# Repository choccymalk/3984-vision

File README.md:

Derived from jkiv/cm4-carriers\

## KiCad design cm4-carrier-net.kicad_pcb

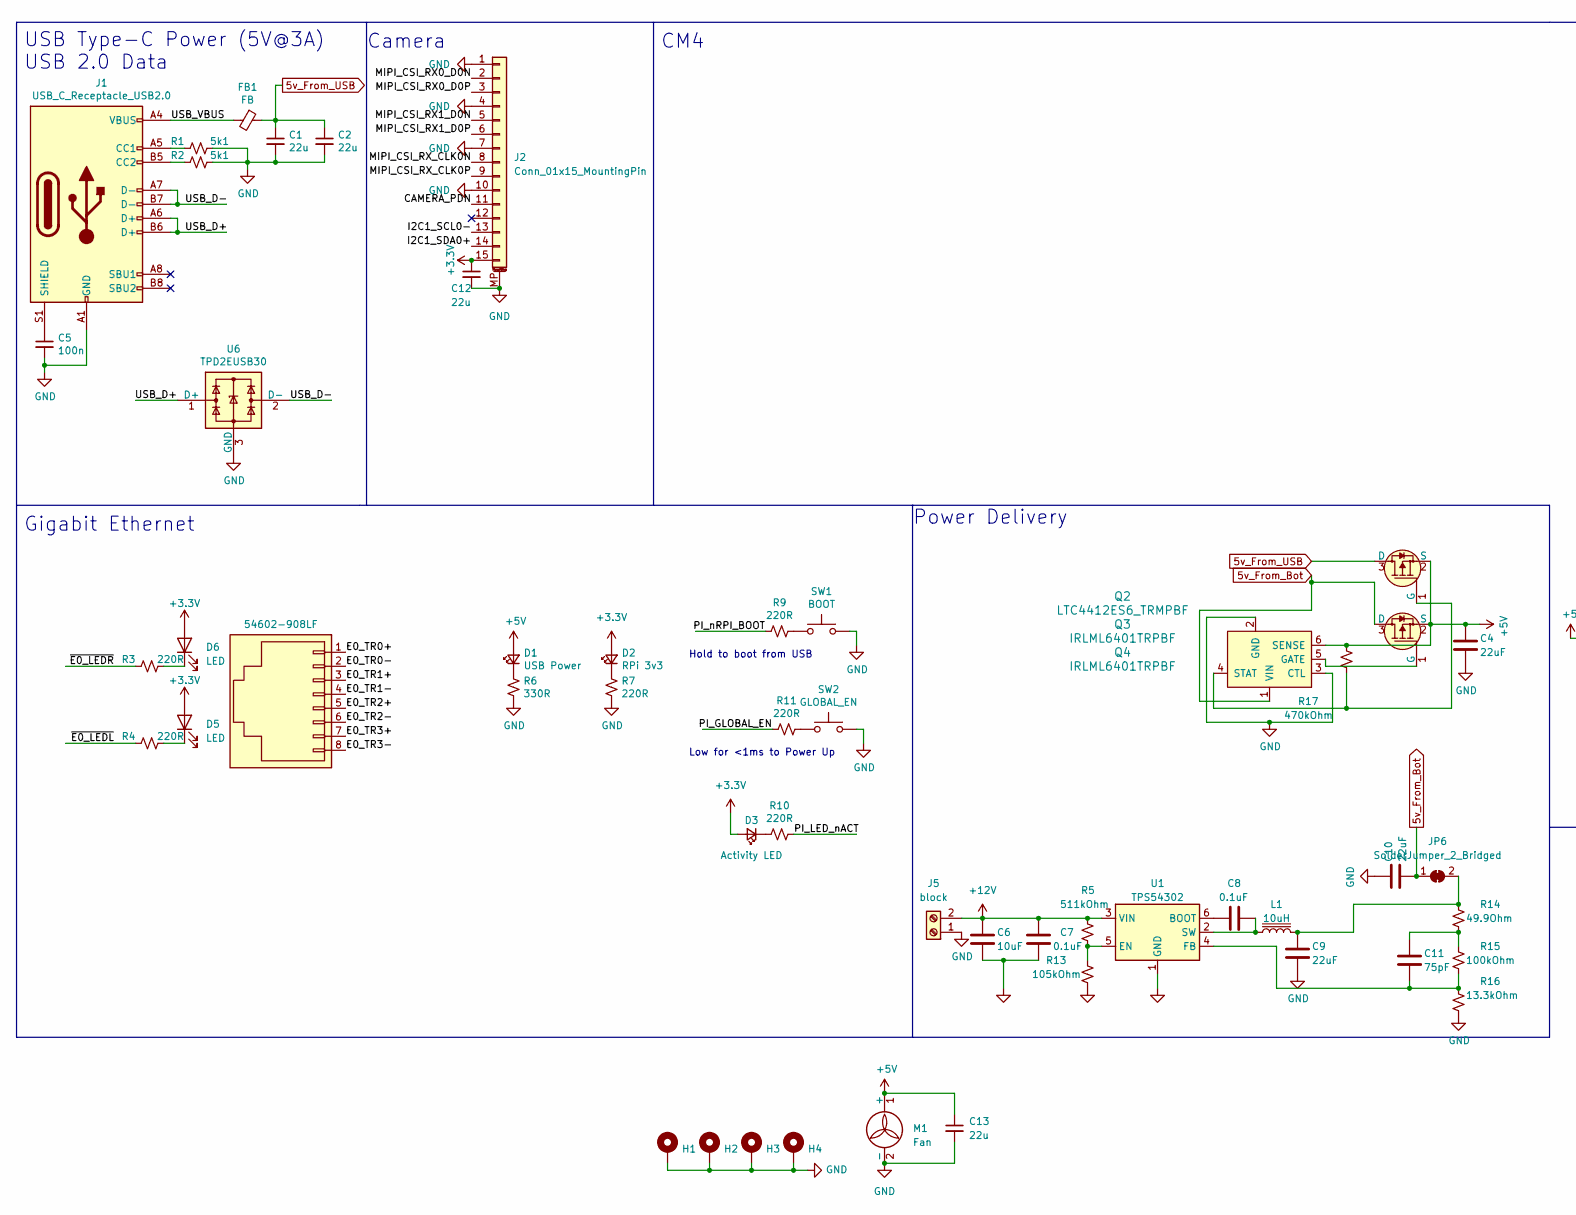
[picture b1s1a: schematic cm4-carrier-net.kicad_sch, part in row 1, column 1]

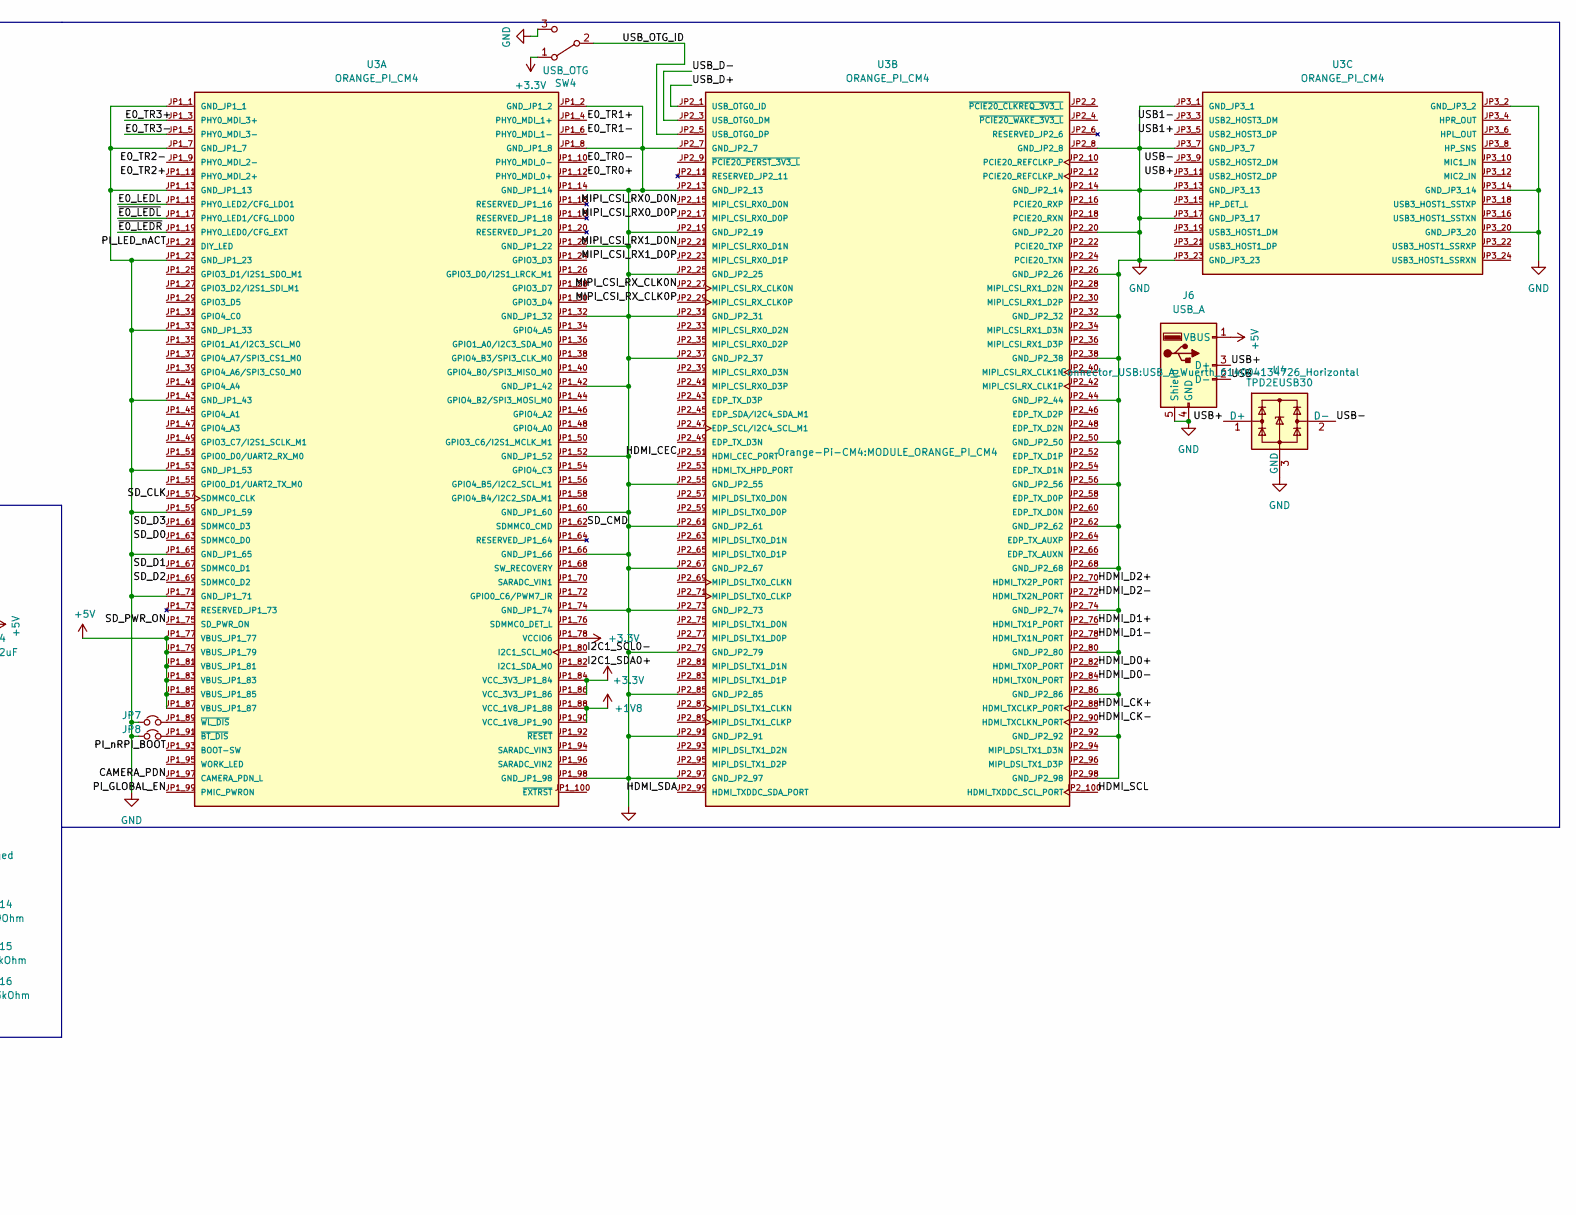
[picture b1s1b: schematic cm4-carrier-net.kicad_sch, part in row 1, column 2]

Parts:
C1, C2, C12, C13: 22u; C_0805_2012Metric
C4, C9, C10: 22uF; C_1206_3216Metric
C5: 100n; C_0805_2012Metric
C6: 10uF; C_1206_3216Metric
C7, C8: 0.1uF; C_1206_3216Metric
C11: 75pF; C_1206_3216Metric
D1: USB Power; LED_0603_1608Metric
D2: RPi 3v3; LED_0603_1608Metric
D3: Activity LED; LED_0603_1608Metric
D5, D6: LED; D_1206_3216Metric_Pad1.42x1.75mm_HandSolder
FB1: FB; L_0805_2012Metric
H1, H2, H3, H4: MountingHole_Pad; MountingHole_2.7mm_M2.5_Pad_Via
J1: USB_C_Receptacle_USB2.0; USB_C_Receptacle_G-Switch_GT-USB-7010ASV
J2: Conn_01x15_MountingPin; Molex_200528-0150_1x15-1MP_P1.00mm_Horizontal
J3: 54602-908LF; Ethernet_Jack_54602-908LF; MPN 54602-908LF; Digi-Key_PN 609-1046-ND
J5: block; TerminalBlock_4Ucon_1x02_P3.50mm_Vertical
J6: USB_A; USB_A_Wuerth_614004134726_Horizontal
JP6: SolderJumper_2_Bridged; SolderJumper-2_P1.3mm_Bridged2Bar_RoundedPad1.0x1.5mm
JP7: ~WL_nDisable; SolderJumper-2_P1.3mm_Bridged2Bar_Pad1.0x1.5mm
JP8: ~BT_nDisable; SolderJumper-2_P1.3mm_Bridged2Bar_Pad1.0x1.5mm
L1: 10uH; L_6.3x6.3_H3
M1: Fan; PinHeader_1x02_P2.54mm_Vertical
Q2: LTC4412ES6_TRMPBF; SOT-23-6; MPN LTC4412ES6#TRMPBF; Digi-Key_PN LTC4412ES6#TRMPBFCT-ND
Q3, Q4: IRLML6401TRPBF; SOT-23-3; MPN IRLML6401TRPBF; Digi-Key_PN IRLML6401PBFCT-ND
R1, R2: 5k1; R_0603_1608Metric
R3, R4, R7, R9, R10, R11: 220R; R_0603_1608Metric
R5: 511kOhm; R_0603_1608Metric
R6: 330R; R_0603_1608Metric
R13: 105kOhm; R_0603_1608Metric
R14: 49.9Ohm; R_0603_1608Metric
R15: 100kOhm; R_0603_1608Metric
R16: 13.3kOhm; R_0603_1608Metric
R17: 470kOhm; R_0603_1608Metric
SW1: BOOT; SW_SPST_B3U-1000P
SW2: GLOBAL_EN; SW_SPST_B3U-1000P
SW4: USB_OTG; SW_SPDT_CK-JS102011SAQN
U1: TPS54302; SOT-23-6
U3: ORANGE_PI_CM4; MODULE_ORANGE_PI_CM4; PARTREV v1.2
U4, U6: TPD2EUSB30; Texas_DRT-3

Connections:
5v_From_Bot: C10.2, JP6.1 (A), Q2.1 (VIN), Q3.3 (D)
5v_From_USB: C1.1, C2.1, FB1.1, Q4.3 (D)
+1V8: U3.JP1_88 (VCC_1V8_JP1_88), U3.JP1_90 (VCC_1V8_JP1_90)
+3.3V: C12.1, D2.2 (A), D3.2 (A), D5.2 (A), D6.2 (A), SW4.1 (A), U3.JP1_78 (VCCIO6), U3.JP1_84 (VCC_3V3_JP1_84), U3.JP1_86 (VCC_3V3_JP1_86); also elsewhere on the board
+5V: C4.1, C13.1, D1.2 (A), J6.1 (VBUS), M1.1 (+), Q2.6 (SENSE), Q3.2 (S), Q4.2 (S), R17.1, U3.JP1_77 (VBUS_JP1_77), U3.JP1_79 (VBUS_JP1_79), U3.JP1_81 (VBUS_JP1_81), U3.JP1_83 (VBUS_JP1_83), U3.JP1_85 (VBUS_JP1_85), U3.JP1_87 (VBUS_JP1_87)
+12V: C6.1, C7.1, J5.2, R5.1, U1.3 (VIN)
/CAMERA_PDN: U3.JP1_97 (CAMERA_PDN_L); also elsewhere on the board
/E0_LEDL: U3.JP1_15 (PHY0_LED2/CFG_LDO1)
/E0_TR0+: J3.1, U3.JP1_12 (PHY0_MDI_0+)
/E0_TR0-: J3.2, U3.JP1_10 (PHY0_MDI_0-)
/E0_TR1+: J3.3, U3.JP1_4 (PHY0_MDI_1+)
/E0_TR1-: J3.4, U3.JP1_6 (PHY0_MDI_1-)
/E0_TR2+: J3.5, U3.JP1_11 (PHY0_MDI_2+)
/E0_TR2-: J3.6, U3.JP1_9 (PHY0_MDI_2-)
/E0_TR3+: J3.7, U3.JP1_3 (PHY0_MDI_3+)
/E0_TR3-: J3.8, U3.JP1_5 (PHY0_MDI_3-)
/HDMI_CEC: U3.JP2_51 (HDMI_CEC_PORT)
/HDMI_CK+: U3.JP2_88 (HDMI_TXCLKP_PORT)
/HDMI_CK-: U3.JP2_90 (HDMI_TXCLKN_PORT)
/HDMI_D0+: U3.JP2_82 (HDMI_TX0P_PORT)
/HDMI_D0-: U3.JP2_84 (HDMI_TX0N_PORT)
/HDMI_D1+: U3.JP2_76 (HDMI_TX1P_PORT)
/HDMI_D1-: U3.JP2_78 (HDMI_TX1N_PORT)
/HDMI_D2+: U3.JP2_70 (HDMI_TX2P_PORT)
/HDMI_D2-: U3.JP2_72 (HDMI_TX2N_PORT)
/HDMI_SCL: U3.JP2_100 (HDMI_TXDDC_SCL_PORT)
/HDMI_SDA: U3.JP2_99 (HDMI_TXDDC_SDA_PORT)
/I2C1_SCL0-: U3.JP1_80 (I2C1_SCL_M0); also elsewhere on the board
/I2C1_SDA0+: U3.JP1_82 (I2C1_SDA_M0); also elsewhere on the board
/MIPI_CSI_RX0_D0N: U3.JP2_15 (MIPI_CSI_RX0_D0N); also elsewhere on the board
/MIPI_CSI_RX0_D0P: U3.JP2_17 (MIPI_CSI_RX0_D0P); also elsewhere on the board
/MIPI_CSI_RX1_D0N: U3.JP2_21 (MIPI_CSI_RX0_D1N); also elsewhere on the board
/MIPI_CSI_RX1_D0P: U3.JP2_23 (MIPI_CSI_RX0_D1P); also elsewhere on the board
/MIPI_CSI_RX_CLK0N: U3.JP2_27 (MIPI_CSI_RX_CLK0N); also elsewhere on the board
/MIPI_CSI_RX_CLK0P: U3.JP2_29 (MIPI_CSI_RX_CLK0P); also elsewhere on the board
/PI_GLOBAL_EN: R11.2, U3.JP1_99 (PMIC_PWRON)
/PI_LED_nACT: R10.1, U3.JP1_21 (DIY_LED)
/PI_nRPI_BOOT: R9.2, U3.JP1_93 (BOOT-SW)
/SD_CLK: U3.JP1_57 (SDMMC0_CLK)
/SD_CMD: U3.JP1_62 (SDMMC0_CMD)
/SD_D0: U3.JP1_63 (SDMMC0_D0)
/SD_D1: U3.JP1_67 (SDMMC0_D1)
/SD_D2: U3.JP1_69 (SDMMC0_D2)
/SD_D3: U3.JP1_61 (SDMMC0_D3)
/SD_PWR_ON: U3.JP1_75 (SD_PWR_ON)
/USB1+: U3.JP3_5 (USB2_HOST3_DP)
/USB1-: U3.JP3_3 (USB2_HOST3_DM)
/USB+: J6.3 (D+), U3.JP3_11 (USB2_HOST2_DP), U4.1 (D+)
/USB-: J6.2 (D-), U3.JP3_9 (USB2_HOST2_DM), U4.2 (D-)
/USB_D+: J1.A6 (D+), J1.B6 (D+), U3.JP2_1 (USB_OTG0_ID), U6.1 (D+)
/USB_D-: J1.A7 (D-), J1.B7 (D-), U3.JP2_3 (USB_OTG0_DM), U6.2 (D-)
/USB_OTG_ID: SW4.2 (B), U3.JP2_5 (USB_OTG0_DP)
/USB_VBUS: FB1.2, J1.A4 (VBUS), J1.A9 (VBUS), J1.B4 (VBUS), J1.B9 (VBUS)
/~E0_LEDL: R4.2, U3.JP1_17 (PHY0_LED1/CFG_LDO0)
/~E0_LEDR: R3.2, U3.JP1_19 (PHY0_LED0/CFG_EXT)
GND: C1.2, C2.2, C4.2, C5.2, C6.2, C7.2, C9.2, C10.1, C12.2, C13.2, H1.1, H2.1, H3.1, H4.1, J1.A1 (GND), J1.A12 (GND), J1.B1 (GND), J1.B12 (GND), J5.1, J6.4 (GND), J6.5 (Shield), JP7.1, JP8.1, M1.2 (-), Q2.2 (GND), Q2.3 (CTL), R1.1, R2.1, R6.2, R7.2, R13.2, R16.2, SW1.2, SW2.2, SW4.3 (C), U1.1 (GND), U3.JP1_1 (GND_JP1_1), U3.JP1_2 (GND_JP1_2), U3.JP1_7 (GND_JP1_7), U3.JP1_8 (GND_JP1_8), U3.JP1_13 (GND_JP1_13), U3.JP1_14 (GND_JP1_14), U3.JP1_22 (GND_JP1_22), U3.JP1_23 (GND_JP1_23), U3.JP1_32 (GND_JP1_32), U3.JP1_33 (GND_JP1_33), U3.JP1_42 (GND_JP1_42), U3.JP1_43 (GND_JP1_43), U3.JP1_52 (GND_JP1_52), U3.JP1_53 (GND_JP1_53), U3.JP1_59 (GND_JP1_59), U3.JP1_60 (GND_JP1_60), U3.JP1_65 (GND_JP1_65), U3.JP1_66 (GND_JP1_66), U3.JP1_71 (GND_JP1_71), U3.JP1_74 (GND_JP1_74), U3.JP1_98 (GND_JP1_98), U3.JP2_7 (GND_JP2_7), U3.JP2_8 (GND_JP2_8), U3.JP2_13 (GND_JP2_13), U3.JP2_14 (GND_JP2_14), U3.JP2_19 (GND_JP2_19), U3.JP2_20 (GND_JP2_20), U3.JP2_25 (GND_JP2_25), U3.JP2_26 (GND_JP2_26), U3.JP2_31 (GND_JP2_31), U3.JP2_32 (GND_JP2_32), U3.JP2_37 (GND_JP2_37), U3.JP2_38 (GND_JP2_38), U3.JP2_44 (GND_JP2_44), U3.JP2_50 (GND_JP2_50), U3.JP2_55 (GND_JP2_55), U3.JP2_56 (GND_JP2_56), U3.JP2_61 (GND_JP2_61), U3.JP2_62 (GND_JP2_62), U3.JP2_67 (GND_JP2_67), U3.JP2_68 (GND_JP2_68), U3.JP2_73 (GND_JP2_73), U3.JP2_74 (GND_JP2_74), U3.JP2_79 (GND_JP2_79), U3.JP2_80 (GND_JP2_80), U3.JP2_85 (GND_JP2_85), U3.JP2_86 (GND_JP2_86), U3.JP2_91 (GND_JP2_91), U3.JP2_92 (GND_JP2_92), U3.JP2_97 (GND_JP2_97), U3.JP2_98 (GND_JP2_98), U3.JP3_1 (GND_JP3_1), U3.JP3_2 (GND_JP3_2), U3.JP3_7 (GND_JP3_7), U3.JP3_13 (GND_JP3_13), U3.JP3_14 (GND_JP3_14), U3.JP3_17 (GND_JP3_17), U3.JP3_20 (GND_JP3_20), U3.JP3_23 (GND_JP3_23), U4.3 (GND), U6.3 (GND); also elsewhere on the board
unnamed: C11.1, R14.2, R15.1
unnamed: D1.1 (K), R6.1
unnamed: D2.1 (K), R7.1
unnamed: D3.1 (K), R10.2
unnamed: D5.1 (K), R4.1
unnamed: D6.1 (K), R3.1
unnamed: J1.A5 (CC1), R1.2
unnamed: J1.B5 (CC2), R2.2
unnamed: C5.1, J1.S1 (SHIELD)
unnamed: C9.1, JP6.2 (B), L1.2, R14.1
unnamed: Q2.5 (GATE), Q3.1 (G)
unnamed: Q2.4 (STAT), Q4.1 (G), R17.2
unnamed: R9.1, SW1.1
unnamed: R11.1, SW2.1
unnamed: C8.1, U1.6 (BOOT)
unnamed: R5.2, R13.1, U1.5 (EN)
unnamed: C11.2, R15.2, R16.1, U1.4 (FB)
unnamed: C8.2, L1.1, U1.2 (SW)
unnamed: JP8.2, U3.JP1_91 (~BT_DIS)
unnamed: JP7.2, U3.JP1_89 (~WL_DIS)

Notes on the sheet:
Camera
Power Delivery
USB Type-C Power (5V@3A) USB 2.0 Data
Hold to boot from USB
Gigabit Ethernet
CM4
Low for <1ms to Power Up

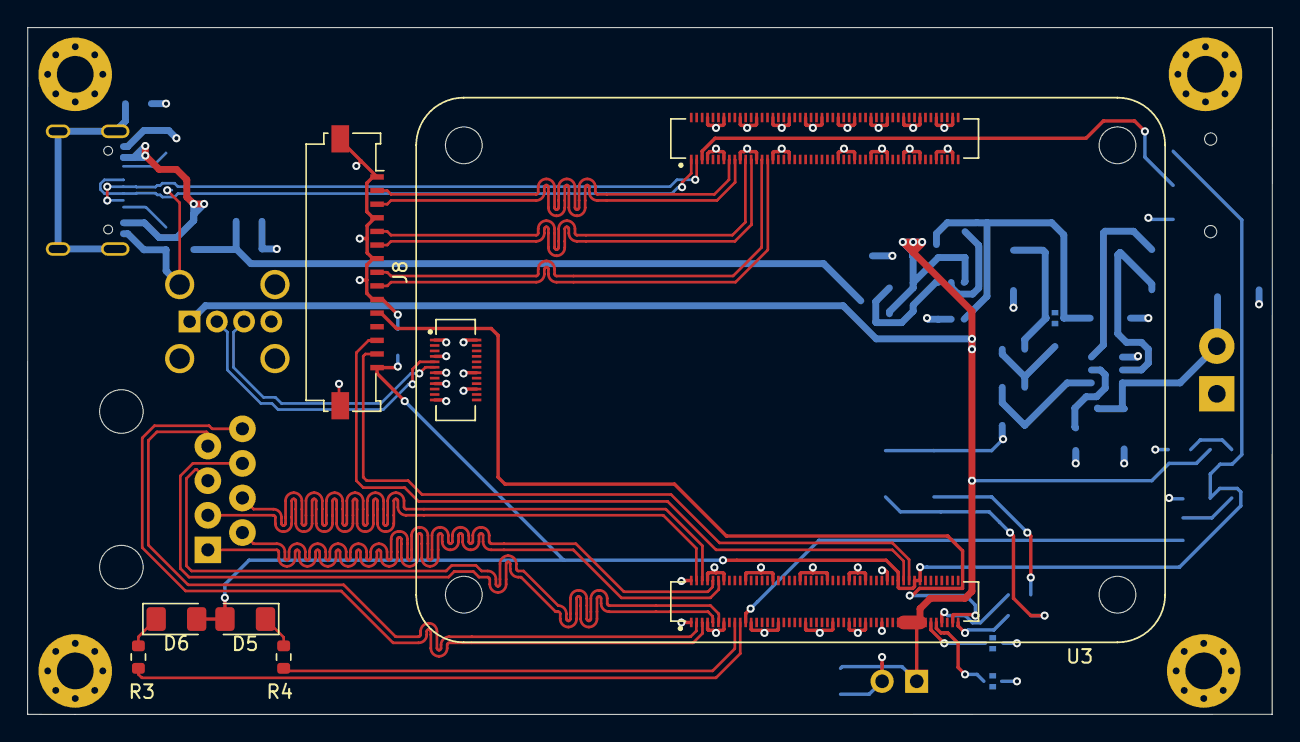
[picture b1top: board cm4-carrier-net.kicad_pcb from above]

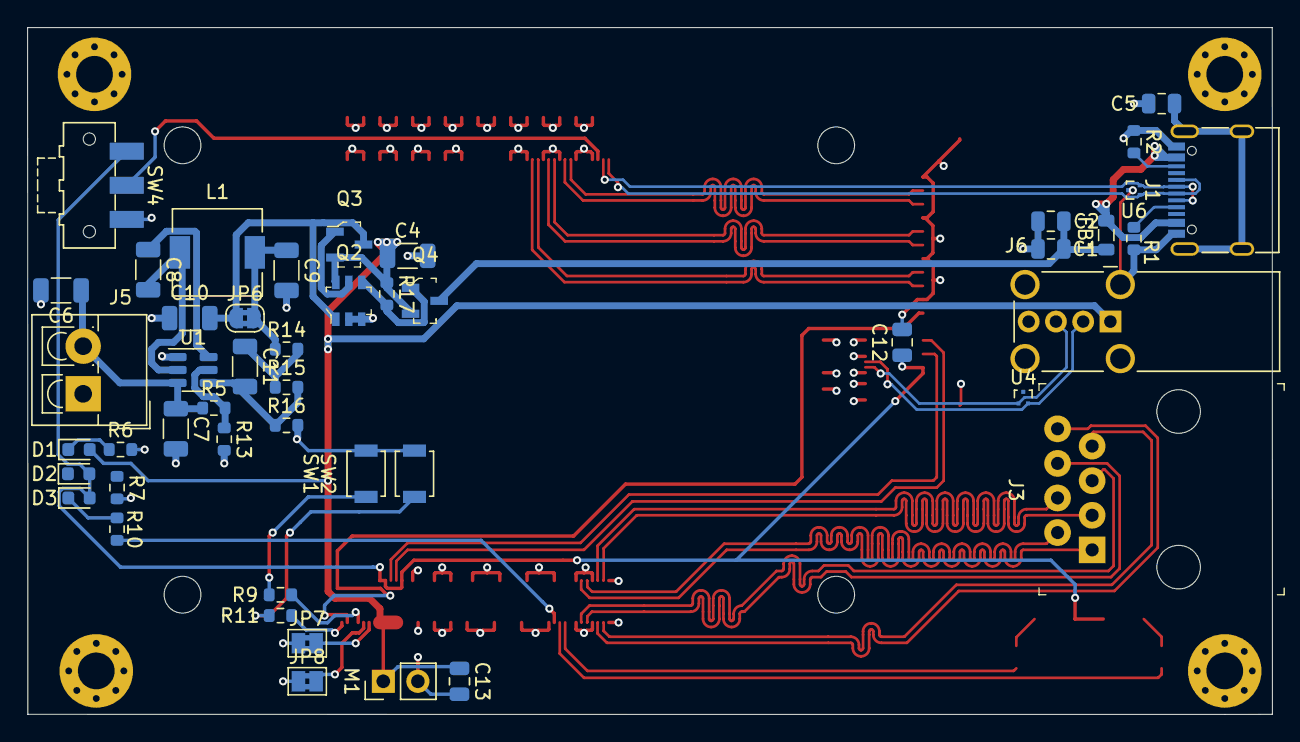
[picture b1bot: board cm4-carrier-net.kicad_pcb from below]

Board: 4 copper layers, 91.4 x 50.4 mm, 57 parts (47 on the bottom side), 55 nets.

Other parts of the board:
J8: Conn_01x15_MountingPin; Molex_200528-0150_1x15-1MP_P1.00mm_Horizontal

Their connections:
+3.3V: J8.15; also elsewhere on the board
/CAMERA_PDN: J8.11; also elsewhere on the board
/I2C1_SCL0-: J8.13; also elsewhere on the board
/I2C1_SDA0+: J8.14; also elsewhere on the board
/MIPI_CSI_RX0_D0N: J8.2; also elsewhere on the board
/MIPI_CSI_RX0_D0P: J8.3; also elsewhere on the board
/MIPI_CSI_RX1_D0N: J8.5; also elsewhere on the board
/MIPI_CSI_RX1_D0P: J8.6; also elsewhere on the board
/MIPI_CSI_RX_CLK0N: J8.8; also elsewhere on the board
/MIPI_CSI_RX_CLK0P: J8.9; also elsewhere on the board
GND: J8.1, J8.4, J8.7, J8.10, J8.MP (MountPin); also elsewhere on the board

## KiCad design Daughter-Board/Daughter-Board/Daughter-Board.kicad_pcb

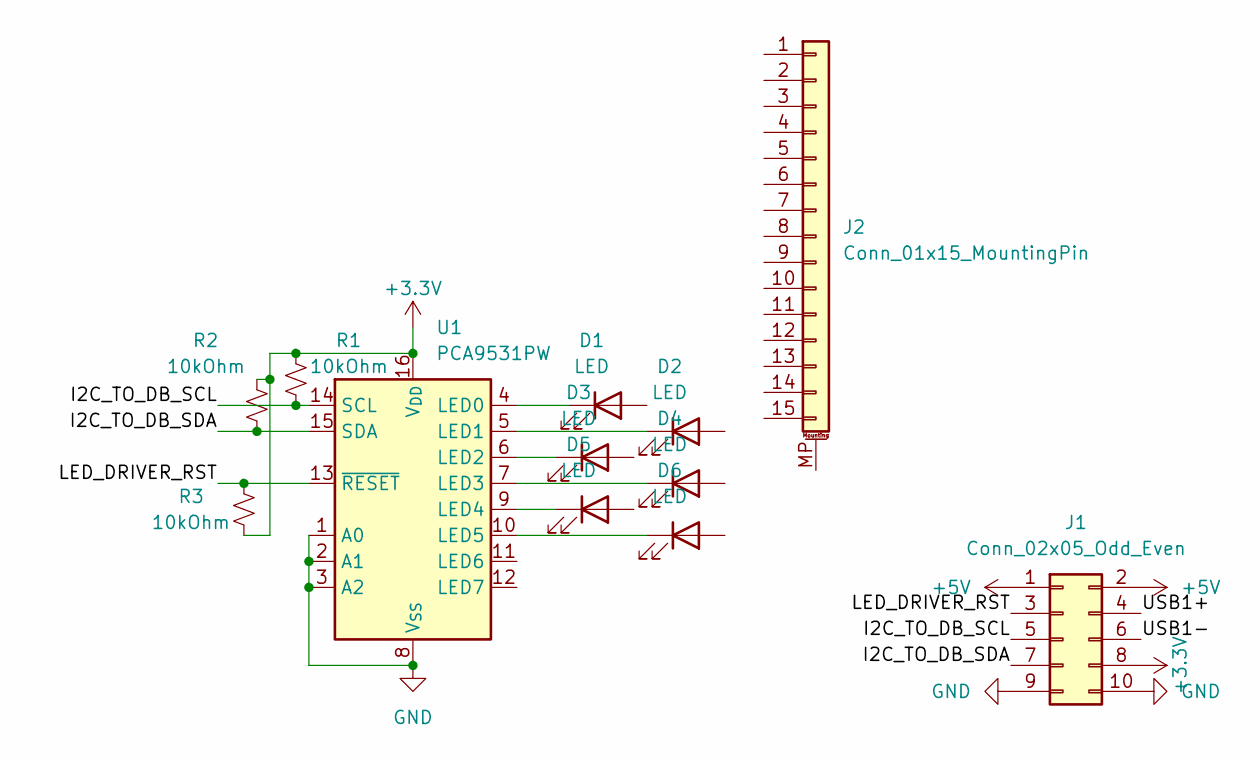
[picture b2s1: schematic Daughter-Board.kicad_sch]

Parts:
D1, D2, D3, D4, D5, D6: LED; LED_1812_4532Metric_Pad1.30x3.40mm_HandSolder
J1: Conn_02x05_Odd_Even; PinSocket_2x05_P1.27mm_Vertical_SMD
J2: Conn_01x15_MountingPin; Molex_200528-0150_1x15-1MP_P1.00mm_Horizontal
R1, R2, R3: 10kOhm; R_0603_1608Metric
U1: PCA9531PW; TSSOP-16_4.4x5mm_P0.65mm

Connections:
+3.3V: J1.8, R1.1, R2.1, R3.1, U1.16 (V_{DD})
+5V: J1.1, J1.2
/I2C_TO_DB_SCL: J1.5, R1.2, U1.14 (SCL)
/I2C_TO_DB_SDA: J1.7, R2.2, U1.15 (SDA)
/LED_DRIVER_RST: J1.3, R3.2, U1.13 (~RESET)
/USB1+: J1.4
/USB1-: J1.6
GND: J1.9, J1.10, U1.1 (A0), U1.2 (A1), U1.3 (A2), U1.8 (V_{SS})
unnamed: D1.1 (K), U1.4 (LED0)
unnamed: D2.1 (K), U1.5 (LED1)
unnamed: D3.1 (K), U1.6 (LED2)
unnamed: D4.1 (K), U1.7 (LED3)
unnamed: D5.1 (K), U1.9 (LED4)
unnamed: D6.1 (K), U1.10 (LED5)

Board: 2 copper layers, 12 parts (0 on the bottom side), 12 nets, no tracks yet.

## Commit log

2024-04-15 Added Banana Pi pinout
2024-04-16 added power protection and some layout changes
2024-04-20 a couple of changes
    fully removed cm4!
    added orange pi cm4 footprint.
    added extra usb 2 port.
    removed unneeded diode.
2024-04-20 removed banana pi pinouts
2024-04-20 added orange pi cm4 pinouts
2024-04-20 added pictures
2024-04-20 added cad model
2024-04-20 changed some things
2024-04-20 added a pin header for the daughter board
2024-04-20 moved a trace
2024-04-20 added thingies
    began creating daughter board and added stm32 for led control
2024-04-20 added some things
2024-04-22 ethernet is routed on the top only now
2024-04-22 added camera zif connector
2024-04-22 tuned length of traces and pairs
2024-04-23 cleaned up pcb routing
2024-04-23 cleaned up the pcb a little bit
2024-04-23 i forgot to refill the ground planes
2024-04-23 i forgot what i changed
2024-04-23 added tvs on the usb a
2024-04-24 added some fun thingies
2024-06-18 redesigned pcb
2024-09-21 google coral tpu
